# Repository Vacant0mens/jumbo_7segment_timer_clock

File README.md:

# Jumbo 7-Segment Clock and Programable Countdown Timer
A clock/timer using a set of large 7-segment two-color digit displays (18 pin, common anode).
Written for MicroPython, but may also work with CircuitPython (untested).

For the circuit, use two-color 12v 7-segment digits with 18 pins and in Common Anode configuration. Adjust circuit resistance as needed/desired/is safe for your hardware. I hold no responsibility for any circuits you create or possess that may or may not be derived from any of my projects. Just keep the magic smoke from escaping, and everything will be fine.

The digits I used have green and red LED's, and lighting them both simultaneously creates a third "amber" color (or more orange-ish or more yellow-ish depending on the brightness of each color). 

The code in this project was written with MicroPython for the Wemos/Lolin D1 Mini. In theory, any ESP8266 board could work fine with the code as-is. Any other MicroPython-compatible board that has an SPI port (i.e. ESP32) could also work if you change the pin names/numbers appropriately. But if you're just wanting to build this quickly without changing much (if anything), use the Lolin D1 Mini, preferably v4, but any revision should work.

The countdown timers can be easily configured by adding/removing/editing strings in the `TIMER_STRINGS` list at the top of `visual_timer.py`. (Note: Time should always be input as 24-hour time, and will always be displayed as such.)

# Getting Started
1. Input your WiFi name and password in the `Clock` class in `clock.py`.
2. Update the `TIMER_STRINGS` list in `visual_timer.py` as needed, in the format `HH:mm:ss:<color>:<True|False>`. Currently only 'red', 'amber', and 'green' are acceptable colors, and the True/False at the end tells the module whether to start a timer at that time (e.g. input 'False' for when a timer ends or to change the color of the clock, input 'True' for all timers that run consecutively.)
3. Flash your microcontroller with the appropriate firmware. I will not cover this since there are lots of tutorials out there.
4. Copy the files to the microcontroller. For MicroPython, use `ampy`. (enter `ampy --help` to get more info on those commands)
   1. You should only need these files: `clock.py`, `main.py`, `visual_timer.py`, and `TPIC6B595_ShiftRegister.py`
5. Connect all the digits in serial with the controller attached to the left-most digit (when looking at the digits' fronts).
   1. It may be possible to orient the digits opposite from this, but you may end up having to write all of your strings and times backwards.

# Code
## Timer
When a timer phase starts, it will illuminate three horizontal lines in each of the lower 5 digits, each line in each digit represents one minute. When the timer has 10 seconds left, it will blink all the segments in (up to) 10 digits in the first second, then flashes one digit less each second until zero. The digits will remain off for a second or two to signify the end of the timer, before either starting the next countdown/timer or displaying the time again.

I chose to run the timer in increments of 15 minutes (or less) because it was fairly easy to write the code for, and it seemed the most flexible while being easy to maintain. It also would've taken way too long to code a dynamic timer that could use up-to all of the digits+segments for the countdown. My setup only has 6 digits and with 7 or 8 segments in each didn't add up to any useful number of minutes. I may address this later.

The timer configuration strings were designed to be string to reduce memory usage instead of having a list of tuples or using a dict. I'm not sure exactly how much memory it saves, but there isn't a lot to work with in the ESP8266.

## Clock
Except while running a timer phase, the clock will display the time in 24-hour time, and will display green from 0:00 to 11:59, and will display red from 12:00 to 23:59.

Since the internal clock in the ESP8266 is really bad at staying accurate, the `clock.py` module will update the time every hour by calling out to worldtimeapi.org.

## main.py
Since there is so little memory to work with in the ESP8266, I had to slim down the modules as much as I could. To help with this, I added some useful `print`'s to show how much memory was being used before/after each import so that I could guage how much memory I had available or had to free up.

## Shift Register
This module I wrote myself based on the documentation/whitepaper for the TPIC6B595 chip. There are a few basic functions to send raw data to the registers and such, and there are a few functions that wrap those to make it easier to use the shift registers as a display. The goal was to make it as easy to use as the MAX7219 chip.
There may be an easier and possibly cleaner way to do this, but I was able to get this working after a lot of troubleshooting and more than a few frustrating read-through's of the document.

There are objects and functions in this module that help to translate the user's string input into something usable by the shift registers and the 7-segment display, while still being at least mostly recognizable as English characters on the display.

The order of the segments and everything had to be designed and built by hand, so there are ascii-art diagrams and lots of comments to keep track of it all.

# Circuit Design
The circuit/s was/were designed in KiCad. I chose the TPCI6B595 shift register because I needed something that could handle the 12v LED's in the displays. I attempted to use a level shifter as well as a logic inverter to boost the logic pins up to 5v, but later found that the TPIC6B595 accepted 3v logic, so it worked out in my favor. The circuit for the controller board might still have a spot to hold the shifter or inverter, but I've bypassed this in my current working setup and will probably fix it in the design if I need to order more circuit boards for it.

The controller board was one of my first circuit board designs and took a few iterations to get it right. The digit boards were mostly done other than I overlooked one through-hole when spacing them out. The resistors you use depend on the LED's that come in the digits you get. Some might have them built into the LED circuit. I had to test out different resistors to get one that didn't make the lights too dim and didn't allow the LED's to get too hot. I also had to use a different resistor for the dot on each digit to balance out the brightness between the dot and the other segments. I assume the difference was because it had only one LED where the other segments have multiple.

The digit boards are designed to be connected in serial, potentially as many as you can power with a single 12v power supply with a barrell jack. It would have been much easier and cleaner to use flat 2x4-pin cables to connect between the boards, but I didn't think of that at the time. It will most likely be included in the next revision.

# Future Plans and Ideas
## Code
1. Make the code easier to get started with/use. i.e. combining all of the configuration objects into a single place (a json file, or just inside `main.py`).
## Circuit
1. Change the connector pins on the digit boards to be compatible with 2x4-pin connectors/headers.
2. Revise the digit boards so that they can either have the microcontroller attached, or have the Serial port/pins attached.
## Bigger Scope (or separate project?)
1. Update hardware (or design a new project) that uses RGB-based 7- or 14-segment displays.
   1. Rip out LED's from single-color displays, replace with RGB LED's and configure them in a similar way.

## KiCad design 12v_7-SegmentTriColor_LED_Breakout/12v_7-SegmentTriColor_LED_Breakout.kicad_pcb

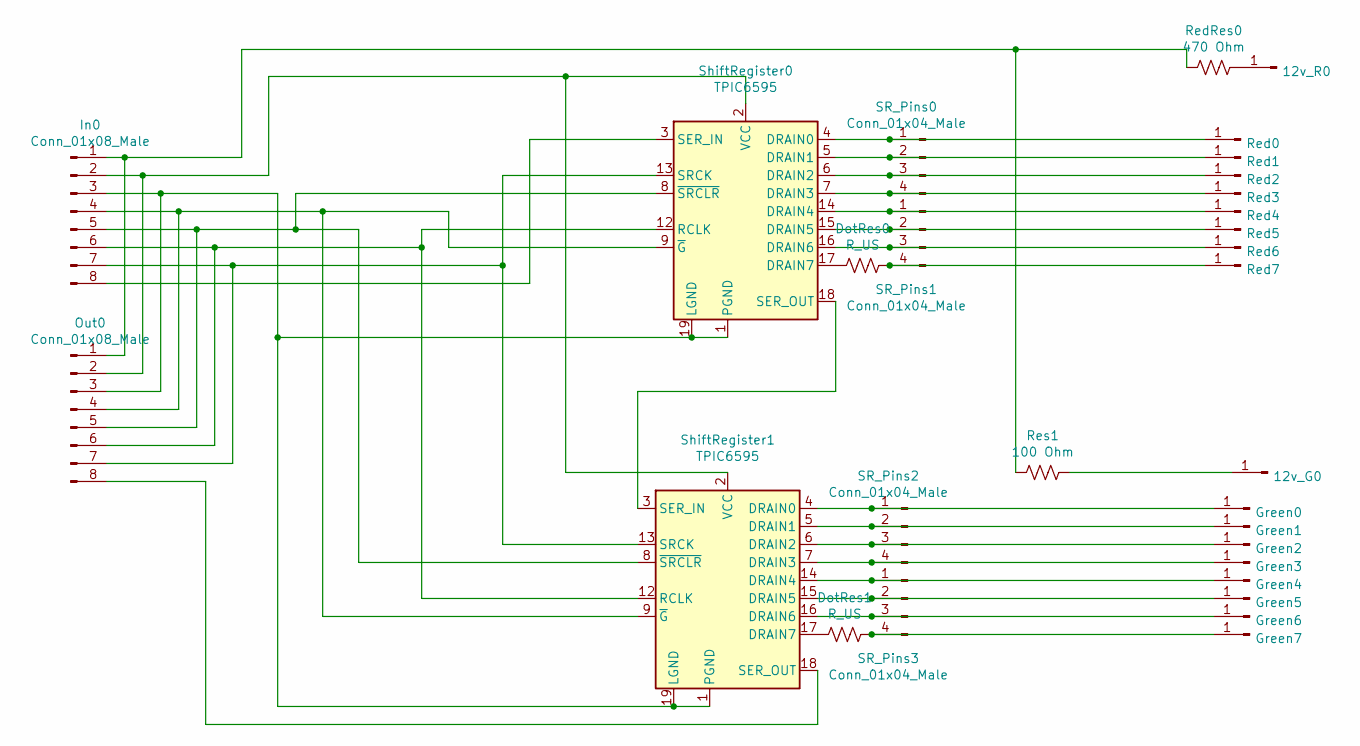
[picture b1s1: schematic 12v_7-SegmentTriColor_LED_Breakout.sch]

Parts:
12v_G0, 12v_R0: Led_12v_Red0; PinHeader_1x01_P2.54mm_Vertical
DotRes0, DotRes1: R_US; R_Axial_DIN0204_L3.6mm_D1.6mm_P5.08mm_Horizontal
Green0, Green1, Green2, Green3, Green4, Green5, Green6, Green7: Led; PinHeader_1x01_P2.54mm_Vertical
In0: Conn_01x08_Male; PinHeader_1x08_P2.54mm_Vertical
Out0: Conn_01x08_Male; PinHeader_1x08_P2.54mm_Vertical
Red0, Red1, Red2, Red3, Red4, Red5, Red6, Red7: Led_12v_Red0; PinHeader_1x01_P2.54mm_Vertical
RedRes0: 470 Ohm; R_Axial_DIN0204_L3.6mm_D1.6mm_P5.08mm_Horizontal
Res1: 100 Ohm; R_Axial_DIN0204_L3.6mm_D1.6mm_P5.08mm_Horizontal
SR_Pins0, SR_Pins1, SR_Pins2, SR_Pins3: Conn_01x04_Male; PinHeader_1x04_P2.54mm_Vertical
ShiftRegister0, ShiftRegister1: TPIC6595; DIP-20_W7.62mm

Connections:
unnamed: 12v_G0.1, Res1.2
unnamed: 12v_R0.1, RedRes0.2
unnamed: DotRes0.1, Red7.1, SR_Pins1.4
unnamed: DotRes0.2, ShiftRegister0.17 (DRAIN7)
unnamed: DotRes1.1, Green7.1, SR_Pins3.4
unnamed: DotRes1.2, ShiftRegister1.17 (DRAIN7)
unnamed: Green0.1, SR_Pins2.1, ShiftRegister1.4 (DRAIN0)
unnamed: Green1.1, SR_Pins2.2, ShiftRegister1.5 (DRAIN1)
unnamed: Green2.1, SR_Pins2.3, ShiftRegister1.6 (DRAIN2)
unnamed: Green3.1, SR_Pins2.4, ShiftRegister1.7 (DRAIN3)
unnamed: Green4.1, SR_Pins3.1, ShiftRegister1.14 (DRAIN4)
unnamed: Green5.1, SR_Pins3.2, ShiftRegister1.15 (DRAIN5)
unnamed: Green6.1, SR_Pins3.3, ShiftRegister1.16 (DRAIN6)
unnamed: In0.1, Out0.1, RedRes0.1, Res1.1
unnamed: In0.2, Out0.2, ShiftRegister0.2 (VCC), ShiftRegister1.2 (VCC)
unnamed: In0.3, Out0.3, ShiftRegister0.1 (PGND), ShiftRegister0.10 (PGND), ShiftRegister0.11 (PGND), ShiftRegister0.19 (LGND), ShiftRegister0.20 (PGND), ShiftRegister1.1 (PGND), ShiftRegister1.10 (PGND), ShiftRegister1.11 (PGND), ShiftRegister1.19 (LGND), ShiftRegister1.20 (PGND)
unnamed: In0.4, Out0.4, ShiftRegister0.9 (~G), ShiftRegister1.9 (~G)
unnamed: In0.5, Out0.5, ShiftRegister0.8 (~SRCLR), ShiftRegister1.8 (~SRCLR)
unnamed: In0.6, Out0.6, ShiftRegister0.12 (RCLK), ShiftRegister1.12 (RCLK)
unnamed: In0.7, Out0.7, ShiftRegister0.13 (SRCK), ShiftRegister1.13 (SRCK)
unnamed: In0.8, ShiftRegister0.3 (SER_IN)
unnamed: Out0.8, ShiftRegister1.18 (SER_OUT)
unnamed: Red0.1, SR_Pins0.1, ShiftRegister0.4 (DRAIN0)
unnamed: Red1.1, SR_Pins0.2, ShiftRegister0.5 (DRAIN1)
unnamed: Red2.1, SR_Pins0.3, ShiftRegister0.6 (DRAIN2)
unnamed: Red3.1, SR_Pins0.4, ShiftRegister0.7 (DRAIN3)
unnamed: Red4.1, SR_Pins1.1, ShiftRegister0.14 (DRAIN4)
unnamed: Red5.1, SR_Pins1.2, ShiftRegister0.15 (DRAIN5)
unnamed: Red6.1, SR_Pins1.3, ShiftRegister0.16 (DRAIN6)
unnamed: ShiftRegister0.18 (SER_OUT), ShiftRegister1.3 (SER_IN)

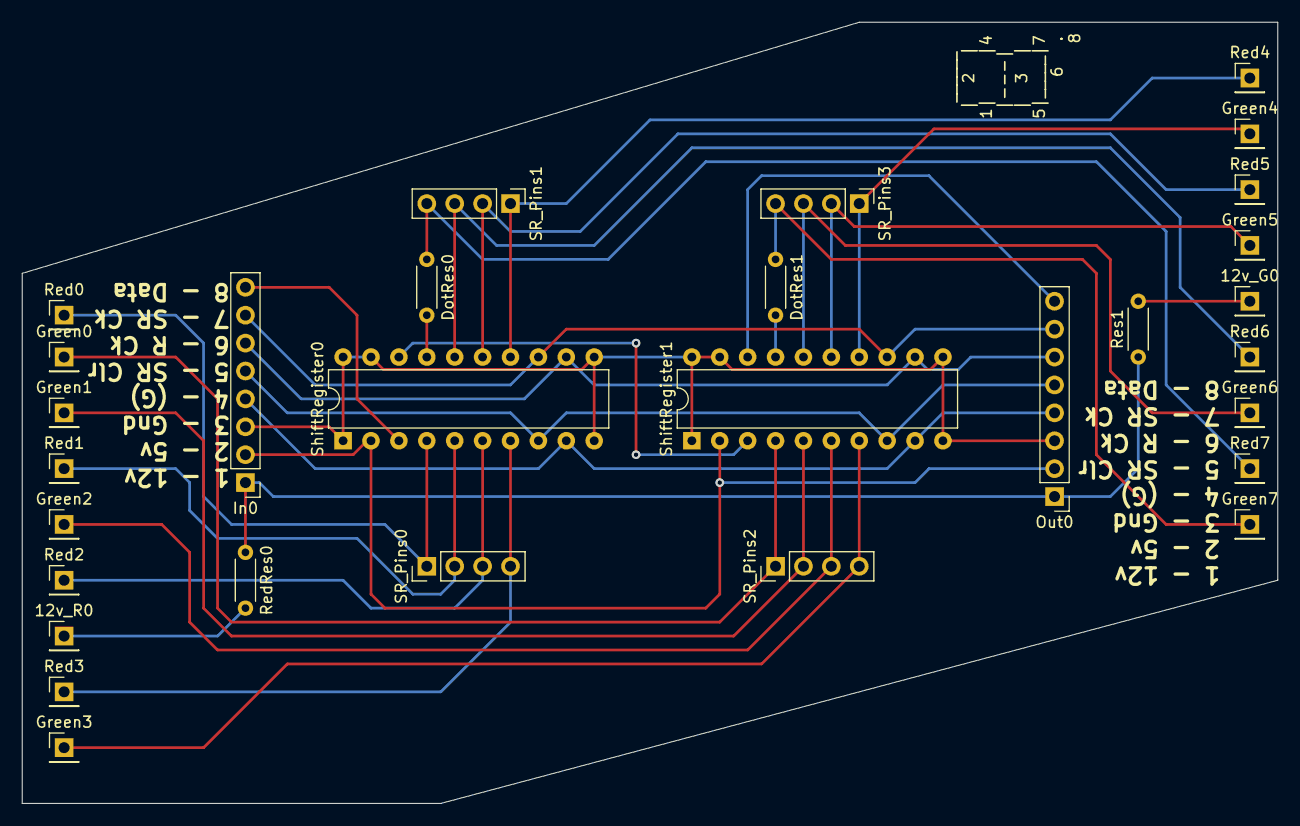
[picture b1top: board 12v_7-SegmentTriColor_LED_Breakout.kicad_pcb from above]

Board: 2 copper layers, 114.3 x 71.1 mm, 30 parts (0 on the bottom side), 30 nets.

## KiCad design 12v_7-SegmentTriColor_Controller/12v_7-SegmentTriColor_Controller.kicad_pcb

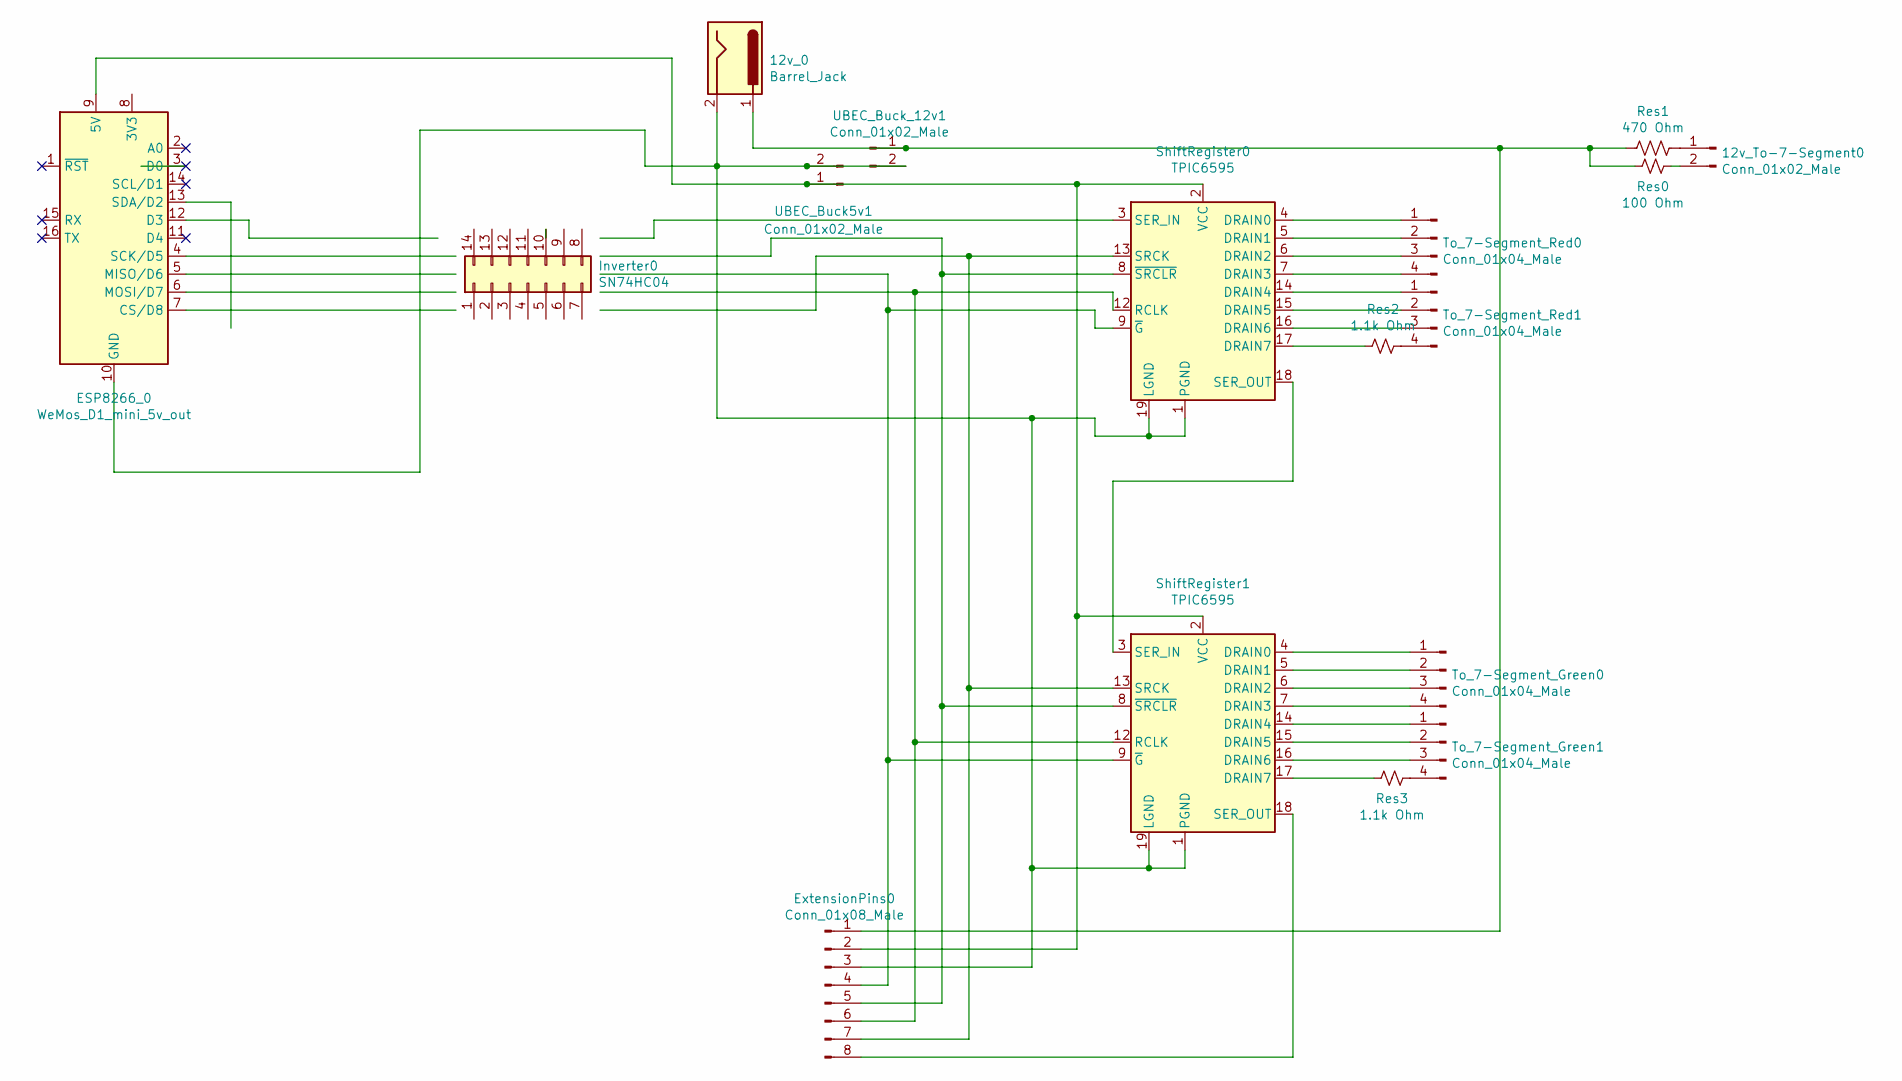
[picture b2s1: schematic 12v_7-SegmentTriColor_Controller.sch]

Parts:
12v_0: Barrel_Jack; BarrelJack_SmallGeneric_Horizontal
12v_To-7-Segment0: Conn_01x02_Male; PinHeader_1x02_P2.54mm_Vertical
ESP8266_0: WeMos_D1_mini_5v_out; WEMOS_D1_mini_light
ExtensionPins0: Conn_01x08_Male; PinHeader_1x08_P2.54mm_Vertical
Inverter0: SN74HC04; DIP-14_W7.62mm
Res0: 100 Ohm; R_Axial_DIN0207_L6.3mm_D2.5mm_P2.54mm_Vertical
Res1: 470 Ohm; R_Axial_DIN0207_L6.3mm_D2.5mm_P2.54mm_Vertical
Res2, Res3: 1.1k Ohm; R_Axial_DIN0207_L6.3mm_D2.5mm_P2.54mm_Vertical
ShiftRegister0, ShiftRegister1: TPIC6595; DIP-20_W7.62mm
To_7-Segment_Green0, To_7-Segment_Green1, To_7-Segment_Red0, To_7-Segment_Red1: Conn_01x04_Male; PinHeader_1x04_P2.54mm_Vertical
UBEC_Buck5v1: Conn_01x02_Male; PinHeader_1x02_P2.54mm_Vertical
UBEC_Buck_12v1: Conn_01x02_Male; PinHeader_1x02_P2.54mm_Vertical

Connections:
unnamed: 12v_0.1, ExtensionPins0.1, Res0.2, Res1.2, UBEC_Buck_12v1.1
unnamed 1: 12v_0.2, ESP8266_0.10 (GND), ExtensionPins0.3, ShiftRegister0.1 (PGND), ShiftRegister0.10 (PGND), ShiftRegister0.11 (PGND), ShiftRegister0.19 (LGND), ShiftRegister0.20 (PGND), ShiftRegister1.1 (PGND), ShiftRegister1.10 (PGND), ShiftRegister1.11 (PGND), ShiftRegister1.19 (LGND), ShiftRegister1.20 (PGND), UBEC_Buck5v1.2, UBEC_Buck_12v1.2; also elsewhere on the board
unnamed: 12v_To-7-Segment0.1, Res1.1
unnamed: 12v_To-7-Segment0.2, Res0.1
unnamed 7: ESP8266_0.4 (SCK/D5); also elsewhere on the board
unnamed 8: ESP8266_0.5 (MISO/D6); also elsewhere on the board
unnamed 9: ESP8266_0.6 (MOSI/D7); also elsewhere on the board
unnamed 10: ESP8266_0.7 (CS/D8); also elsewhere on the board
unnamed 11: ESP8266_0.8 (3V3); also elsewhere on the board
unnamed 12: ESP8266_0.9 (5V), ExtensionPins0.2, ShiftRegister0.2 (VCC), ShiftRegister1.2 (VCC), UBEC_Buck5v1.1; also elsewhere on the board
unnamed 14: ESP8266_0.12 (D3); also elsewhere on the board
unnamed 15: ESP8266_0.13 (SDA/D2); also elsewhere on the board
unnamed 19: ExtensionPins0.4, ShiftRegister0.9 (~G), ShiftRegister1.9 (~G); also elsewhere on the board
unnamed 20: ExtensionPins0.5, ShiftRegister0.8 (~SRCLR), ShiftRegister1.8 (~SRCLR); also elsewhere on the board
unnamed 21: ExtensionPins0.6, ShiftRegister0.12 (RCLK), ShiftRegister1.12 (RCLK); also elsewhere on the board
unnamed 22: ExtensionPins0.7, ShiftRegister0.13 (SRCK), ShiftRegister1.13 (SRCK); also elsewhere on the board
unnamed: ExtensionPins0.8, ShiftRegister1.18 (SER_OUT)
unnamed 30: ShiftRegister0.3 (SER_IN); also elsewhere on the board
unnamed: Res2.1, To_7-Segment_Red1.4
unnamed: Res2.2, ShiftRegister0.17 (DRAIN7)
unnamed: Res3.1, To_7-Segment_Green1.4
unnamed: Res3.2, ShiftRegister1.17 (DRAIN7)
unnamed: ShiftRegister0.4 (DRAIN0), To_7-Segment_Red0.1
unnamed: ShiftRegister0.5 (DRAIN1), To_7-Segment_Red0.2
unnamed: ShiftRegister0.6 (DRAIN2), To_7-Segment_Red0.3
unnamed: ShiftRegister0.7 (DRAIN3), To_7-Segment_Red0.4
unnamed: ShiftRegister0.14 (DRAIN4), To_7-Segment_Red1.1
unnamed: ShiftRegister0.15 (DRAIN5), To_7-Segment_Red1.2
unnamed: ShiftRegister0.16 (DRAIN6), To_7-Segment_Red1.3
unnamed: ShiftRegister0.18 (SER_OUT), ShiftRegister1.3 (SER_IN)
unnamed: ShiftRegister1.4 (DRAIN0), To_7-Segment_Green0.1
unnamed: ShiftRegister1.5 (DRAIN1), To_7-Segment_Green0.2
unnamed: ShiftRegister1.6 (DRAIN2), To_7-Segment_Green0.3
unnamed: ShiftRegister1.7 (DRAIN3), To_7-Segment_Green0.4
unnamed: ShiftRegister1.14 (DRAIN4), To_7-Segment_Green1.1
unnamed: ShiftRegister1.15 (DRAIN5), To_7-Segment_Green1.2
unnamed: ShiftRegister1.16 (DRAIN6), To_7-Segment_Green1.3

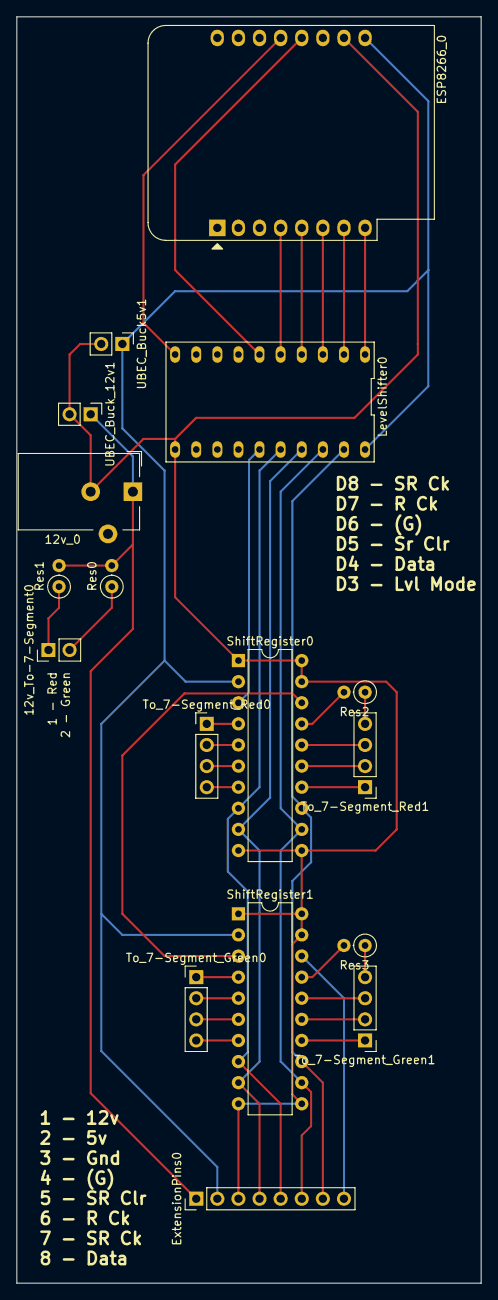
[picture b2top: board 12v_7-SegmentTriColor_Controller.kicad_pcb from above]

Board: 2 copper layers, 55.9 x 152.4 mm, 17 parts (0 on the bottom side), 37 nets.

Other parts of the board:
LevelShifter0: TXS0108EPW; DIP-2x20_10.16mm_2.54mm_pitch_Flipped_pins_1-2_19-20

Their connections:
unnamed 1: LevelShifter0.11; also elsewhere on the board
unnamed 7: LevelShifter0.5; also elsewhere on the board
unnamed 8: LevelShifter0.4; also elsewhere on the board
unnamed 9: LevelShifter0.3; also elsewhere on the board
unnamed 10: LevelShifter0.1; also elsewhere on the board
unnamed 11: LevelShifter0.2; also elsewhere on the board
unnamed 12: LevelShifter0.19; also elsewhere on the board
unnamed 14: LevelShifter0.6; also elsewhere on the board
unnamed 15: LevelShifter0.10; also elsewhere on the board
unnamed 19: LevelShifter0.17; also elsewhere on the board
unnamed 20: LevelShifter0.16; also elsewhere on the board
unnamed 21: LevelShifter0.18; also elsewhere on the board
unnamed 22: LevelShifter0.20; also elsewhere on the board
unnamed 30: LevelShifter0.15; also elsewhere on the board

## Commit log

2024-04-15 first commit of python files
2024-04-15 ignore .vscode folder
2024-04-15 added comment
2024-04-20 added Readme content
2024-04-27 added KiCad project files and gerber files for controller board
2024-04-27 Added KiCad project files and gerber files for 7-segment backplate
